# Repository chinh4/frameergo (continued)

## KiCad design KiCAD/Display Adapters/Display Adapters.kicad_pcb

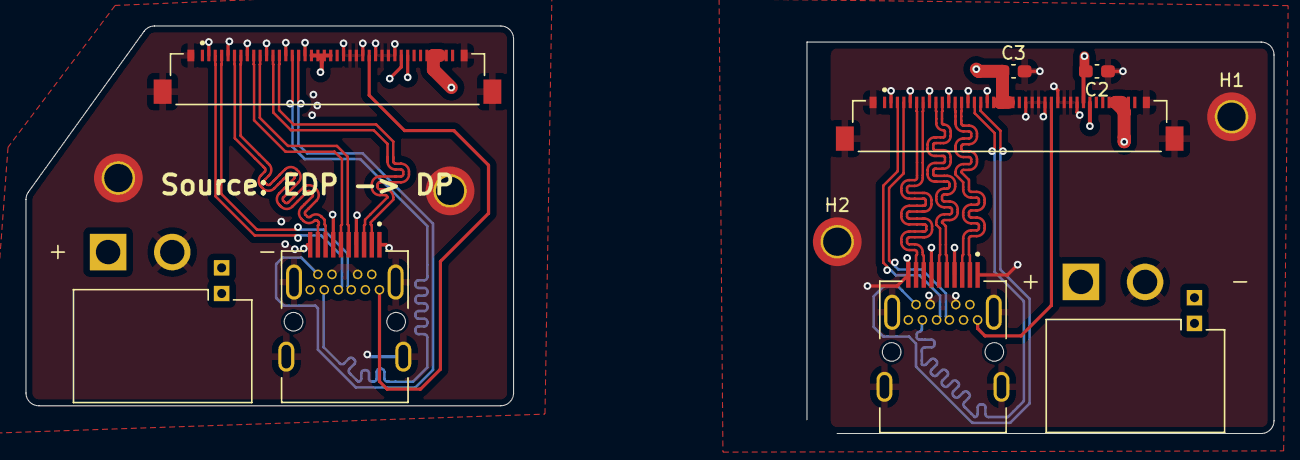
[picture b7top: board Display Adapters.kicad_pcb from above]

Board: 4 copper layers, 97.3 x 31.8 mm, 12 parts (0 on the bottom side), 16 nets.

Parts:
C2, C3: 1uF; C_0603_1608Metric_Pad1.08x0.95mm_HandSolder
H1, H1#2, H2, H2#2: MountingHole_Pad; MountingHole_2.2mm_M2_DIN965_Pad_TopBottom
J1, J6: 20455-040E-76; IPEX_20455-040E-76
J2, J5: G46M2013201AWEU; AMPHENOL_G46M2013201AWEU
J3, J4: XT30PW_2_2_-M.G.B; AMASS_XT30PW_2_2_-M.G.B

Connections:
0_EDP_TX_N: J1.12, J2.5 (ML_LANE0_N), J5.5 (ML_LANE0_N), J6.12
0_EDP_TX_P: J1.13, J2.3 (ML_LANE0_P), J5.3 (ML_LANE0_P), J6.13
1_EDP_TX_N: J1.9, J2.11 (ML_LANE1_N), J5.11 (ML_LANE1_N), J6.9
1_EDP_TX_P: J1.10, J2.9 (ML_LANE1_P), J5.9 (ML_LANE1_P), J6.10
2_EDP_TX_N: J1.6, J2.17 (ML_LANE2_N), J5.17 (ML_LANE2_N), J6.6
2_EDP_TX_P: J1.7, J2.15 (ML_LANE2_P), J5.15 (ML_LANE2_P), J6.7
3_EDP_TX_N: J1.3, J2.12 (ML_LANE3_N), J5.12 (ML_LANE3_N), J6.3
3_EDP_TX_P: J1.4, J2.10 (ML_LANE3_P), J5.10 (ML_LANE3_P), J6.4
+3.3V: C3.1, J1.18, J1.19, J1.20, J1.21, J2.4 (CONFIG1), J2.6 (CONFIG2), J2.20 (DP_PWR), J5.4 (CONFIG1), J5.6 (CONFIG2), J5.20 (DP_PWR), J6.18, J6.19, J6.20, J6.21
+5V: J1.36, J1.37, J1.38, J1.39, J3.P, J4.P, J6.36, J6.37, J6.38, J6.39
AUX_N: J1.16, J2.18 (AUX_CH_N), J5.18 (AUX_CH_N), J6.16
AUX_P: J1.15, J2.16 (AUX_CH_P), J5.16 (AUX_CH_P), J6.15
BLK_OFF_N: C2.2, J1.32, J3.S2, J4.S2, J6.32
BLK_PWM_LCD: J1.33, J3.S1, J4.S1, J6.33
EDP_HPD: J1.27, J2.2 (HOTPLUG_DETECT), J5.2 (HOTPLUG_DETECT), J6.27
GND: C2.1, C3.2, H1.1, H1#2.1, H2.1, H2#2.1, J1.2, J1.5, J1.8, J1.11, J1.14, J1.17, J1.23, J1.24, J1.25, J1.26, J1.28, J1.29, J1.30, J1.31, J1.S1 (SHIELD), J1.S2 (SHIELD), J1.S3 (SHIELD), J1.S4 (SHIELD), J2.1 (GND_1), J2.7 (GND_7), J2.8 (GND_8), J2.13 (GND_13), J2.14 (GND_14), J2.19 (GND_19), J2.S1 (SHIELD), J2.S2 (SHIELD), J2.S3 (SHIELD), J2.S4 (SHIELD), J3.N, J4.N, J5.1 (GND_1), J5.7 (GND_7), J5.8 (GND_8), J5.13 (GND_13), J5.14 (GND_14), J5.19 (GND_19), J5.S1 (SHIELD), J5.S2 (SHIELD), J5.S3 (SHIELD), J5.S4 (SHIELD), J6.2, J6.5, J6.8, J6.11, J6.14, J6.17, J6.23, J6.24, J6.25, J6.26, J6.28, J6.29, J6.30, J6.31, J6.S1 (SHIELD), J6.S2 (SHIELD), J6.S3 (SHIELD), J6.S4 (SHIELD)

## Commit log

2025-12-03 move into separate projects, fix wrong trace length on source
2025-12-05 add ground vias around usb vias
2025-12-07 fix schematics
2025-12-11 start some cad
2025-12-18 USB Hub V2
2025-12-30 bigger pads
2025-12-30 new i.c.
2025-12-31 base config
2026-01-06 label
2026-01-08 mountihing holes
2026-01-09 stuff
2026-01-11 what
2026-01-13 some constraints
2026-01-14 chassis base plate with mounting holes
2026-01-15 assemble
2026-01-16 battery constraints
2026-01-20 batery
2026-01-20 wififififiif
2026-01-21 assemblelvy
2026-01-22 portsupport
2026-01-23 lksjdaajklsfljkf;s
2026-01-25 hatehatehatehate
    i hate inventor
2026-01-25 move to onshape lol
2026-01-26 idek
2026-01-27 add some stuffs
2026-01-31 blendy mc blend
2026-03-03 work on making it ready for submission
2026-03-04 aaaa
2026-03-06 combined
2026-03-10 bomb
2026-03-10 all the csvs
2026-03-11 some tuff
2026-03-11 redners
2026-03-11 typttptpt ypit typo!
2026-03-11 remremremr ermoeve
2026-03-11 cuh cuh cad
2026-03-11 far ffar abaway
2026-03-11 carts
2026-03-11 change display cable
2026-03-12 add forgotten component
2026-03-12 forgot to add this to the bom
2026-03-12 update image
2026-04-06 asdfasdf
